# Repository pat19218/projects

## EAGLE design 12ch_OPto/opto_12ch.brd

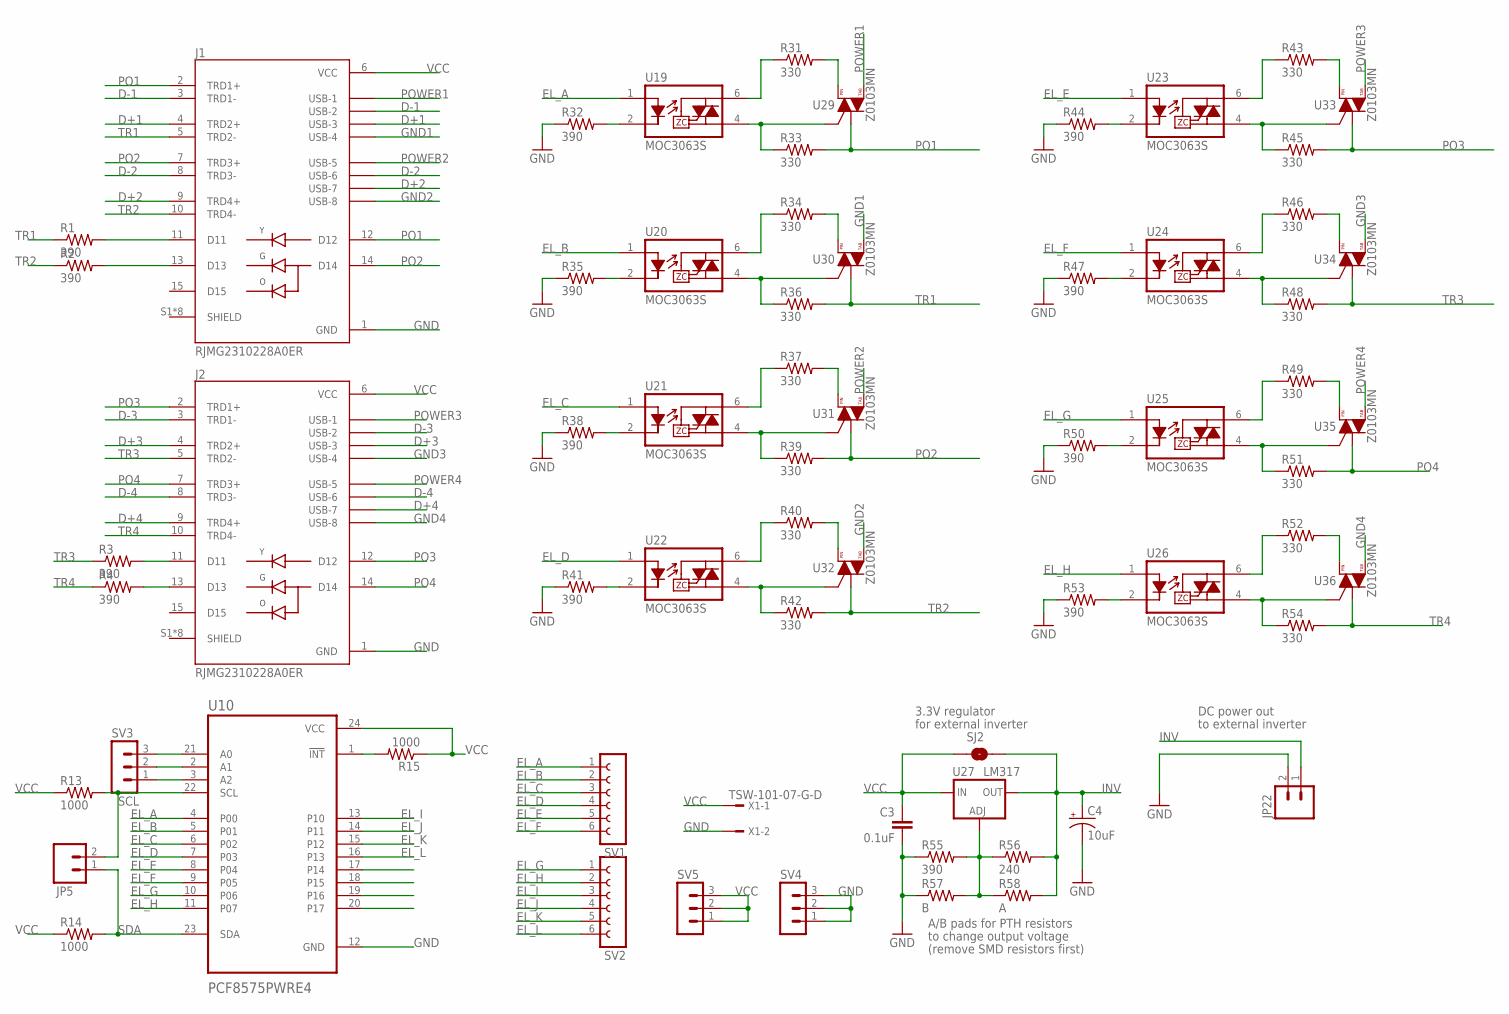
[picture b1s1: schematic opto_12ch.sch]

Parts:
C3: 0.1uF; 0603-CAP
C4: 10uF; EIA3216
J1, J2: RJMG2310228A0ER; AMPHENOL_RJMG2310228A0ER
JP5, JP22: M02PTH; 1X02
R1, R2, R3, R4, R32, R35, R38, R41, R44, R47, R50, R53, R55: 390; 0603-RES
R13, R14, R15: 1000; 0603-RES
R31, R33, R34, R36, R37, R39, R40, R42, R43, R45, R46, R48, R49, R51, R52, R54: 330; 0603-RES
R56: 240; 0603-RES
R57: B; AXIAL-0.4
R58: A; AXIAL-0.4
SJ2: SOLDERJUMPERNO; SJ_2S-NO
SV1, SV2: FE06-1; FE06
SV3, SV4, SV5: MA03-1
U10: PCF8575PWRE4; SOP65P640X120-24N
U19, U20, U21, U22, U23, U24, U25, U26: MOC3063S; DIP8SMD
U27: LM317; V-REG_DPACK
U29, U30, U31, U32, U33, U34, U35, U36: Z0103MN; SOT223
X1: TSW-101-07-G-D; TSW-101-XX-G-D

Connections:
D+1: J1.4 (TRD2+), J1.U13 (USB-3)
D+2: J1.9 (TRD4+), J1.U23 (USB-7)
D+3: J2.4 (TRD2+), J2.U13 (USB-3)
D+4: J2.9 (TRD4+), J2.U23 (USB-7)
D-1: J1.3 (TRD1-), J1.U12 (USB-2)
D-2: J1.8 (TRD3-), J1.U22 (USB-6)
D-3: J2.3 (TRD1-), J2.U12 (USB-2)
D-4: J2.8 (TRD3-), J2.U22 (USB-6)
EL_A: SV1.1, U10.4 (P00), U19.1 (A)
EL_B: SV1.2, U10.5 (P01), U20.1 (A)
EL_C: SV1.3, U10.6 (P02), U21.1 (A)
EL_D: SV1.4, U10.7 (P03), U22.1 (A)
EL_E: SV1.5, U10.8 (P04), U23.1 (A)
EL_F: SV1.6, U10.9 (P05), U24.1 (A)
EL_G: SV2.1, U10.10 (P06), U25.1 (A)
EL_H: SV2.2, U10.11 (P07), U26.1 (A)
EL_I: SV2.3, U10.13 (P10)
EL_J: SV2.4, U10.14 (P11)
EL_K: SV2.5, U10.15 (P12)
EL_L: SV2.6, U10.16 (P13)
GND: C3.2, C4.C (-), J1.1 (GND), J2.1 (GND), JP22.2, R32.1, R35.1, R38.1, R41.1, R44.1, R47.1, R50.1, R53.1, R55.1, R57.P$1 (1), SV4.1, SV4.2, SV4.3, U10.12 (GND), X1.2
GND1: J1.U14 (USB-4), U30.4 (T2)
GND2: J1.U24 (USB-8), U32.4 (T2)
GND3: J2.U14 (USB-4), U34.4 (T2)
GND4: J2.U24 (USB-8), U36.4 (T2)
INV: C4.A (+), JP22.1, R56.2, R58.P$2 (2), SJ2.2, U27.4 (OUT)
unnamed: J2.11 (D11), R3.2
unnamed: J2.13 (D13), R4.2
unnamed: SV3.3, U10.21 (A0)
unnamed: SV3.2, U10.2 (A1)
unnamed: SV3.1, U10.3 (A2)
unnamed: R15.2, U10.1 (!INT)
unnamed: J1.11 (D11), R1.2
unnamed: J1.13 (D13), R2.2
unnamed: R33.1, U19.4 (T2), U29.3 (G)
unnamed: R32.2, U19.2 (K)
unnamed: R31.1, U19.6 (T1)
unnamed: R36.1, U20.4 (T2), U30.3 (G)
unnamed: R35.2, U20.2 (K)
unnamed: R34.1, U20.6 (T1)
unnamed: R39.1, U21.4 (T2), U31.3 (G)
unnamed: R38.2, U21.2 (K)
unnamed: R37.1, U21.6 (T1)
unnamed: R42.1, U22.4 (T2), U32.3 (G)
unnamed: R41.2, U22.2 (K)
unnamed: R40.1, U22.6 (T1)
unnamed: R45.1, U23.4 (T2), U33.3 (G)
unnamed: R44.2, U23.2 (K)
unnamed: R43.1, U23.6 (T1)
unnamed: R48.1, U24.4 (T2), U34.3 (G)
unnamed: R47.2, U24.2 (K)
unnamed: R46.1, U24.6 (T1)
unnamed: R51.1, U25.4 (T2), U35.3 (G)
unnamed: R50.2, U25.2 (K)
unnamed: R49.1, U25.6 (T1)
unnamed: R54.1, U26.4 (T2), U36.3 (G)
unnamed: R53.2, U26.2 (K)
unnamed: R52.1, U26.6 (T1)
unnamed: R55.2, R56.1, R57.P$2 (2), R58.P$1 (1), U27.1 (ADJ)
unnamed: R31.2, U29.2 (T2)
unnamed: R34.2, U30.2 (T2)
unnamed: R37.2, U31.2 (T2)
unnamed: R40.2, U32.2 (T2)
unnamed: R43.2, U33.2 (T2)
unnamed: R46.2, U34.2 (T2)
unnamed: R49.2, U35.2 (T2)
unnamed: R52.2, U36.2 (T2)
PO1: J1.2 (TRD1+), J1.12 (D12), R33.2, U29.1 (T1)
PO2: J1.7 (TRD3+), J1.14 (D14), R39.2, U31.1 (T1)
PO3: J2.2 (TRD1+), J2.12 (D12), R45.2, U33.1 (T1)
PO4: J2.7 (TRD3+), J2.14 (D14), R51.2, U35.1 (T1)
POWER1: J1.U11 (USB-1), U29.4 (T2)
POWER2: J1.U21 (USB-5), U31.4 (T2)
POWER3: J2.U11 (USB-1), U33.4 (T2)
POWER4: J2.U21 (USB-5), U35.4 (T2)
SCL: JP5.2, R13.2, U10.22 (SCL)
SDA: JP5.1, R14.2, U10.23 (SDA)
TR1: J1.5 (TRD2-), R1.1, R36.2, U30.1 (T1)
TR2: J1.10 (TRD4-), R2.1, R42.2, U32.1 (T1)
TR3: J2.5 (TRD2-), R3.1, R48.2, U34.1 (T1)
TR4: J2.10 (TRD4-), R4.1, R54.2, U36.1 (T1)
VCC: C3.1, J1.6 (VCC), J2.6 (VCC), R13.1, R14.1, R15.1, SJ2.1, SV5.1, SV5.2, SV5.3, U10.24 (VCC), U27.3 (IN), X1.1

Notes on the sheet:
DC power out
to external inverter
3.3V regulator
for external inverter
A/B pads for PTH resistors
to change output voltage
(remove SMD resistors first)

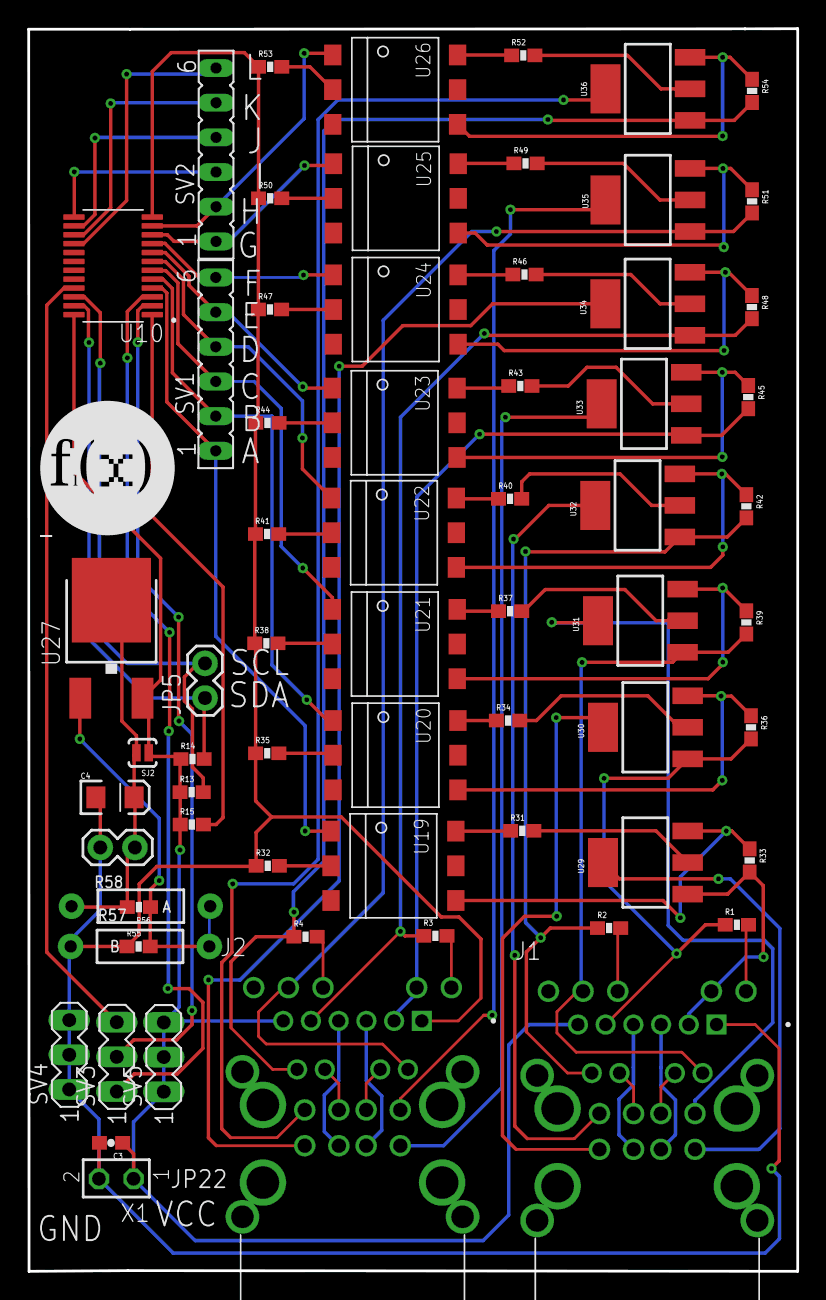
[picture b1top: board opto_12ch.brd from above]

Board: 2 copper layers, 56.3 x 91.0 mm, 66 parts (0 on the bottom side), 82 nets.

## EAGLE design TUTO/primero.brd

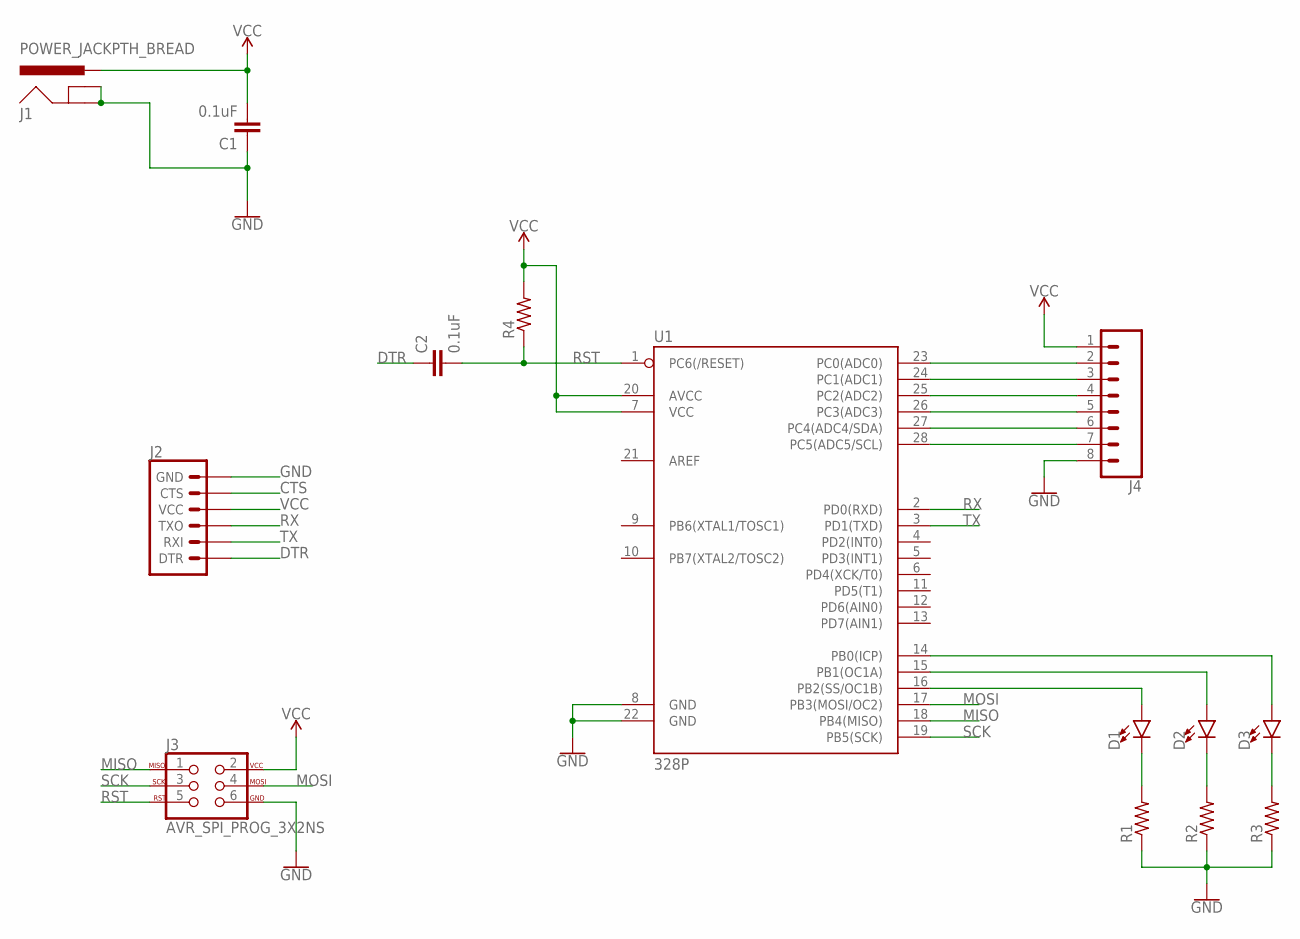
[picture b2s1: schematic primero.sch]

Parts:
C1, C2: 0.1uF; CAP-PTH-SMALL-KIT
D1, D2, D3: LED5MM; LED_5MM
J1: POWER_JACKPTH_BREAD; POWER_JACK_PTH_BREAD
J2: 6_PIN_SERIAL_TARGET; 1X06
J3: AVR_SPI_PROG_3X2NS; 2X3-NS
J4: CONN_08"; 1X08
R1, R2, R3, R4: R-US_0204/5; 0204/5
U1: 328P; DIP28

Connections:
CTS: J2.5 (CTS)
DTR: C2.1, J2.1 (DTR)
GND: C1.1, J1.GND, J1.GNDBREAK, J2.6 (GND), J3.6, J4.8, R1.1, R2.1, R3.1, U1.8 (GND), U1.22 (GND)
MISO: J3.1, U1.18 (PB4(MISO))
MOSI: J3.4, U1.17 (PB3(MOSI/OC2))
unnamed: J4.2, U1.23 (PC0(ADC0))
unnamed: J4.3, U1.24 (PC1(ADC1))
unnamed: J4.4, U1.25 (PC2(ADC2))
unnamed: J4.5, U1.26 (PC3(ADC3))
unnamed: J4.6, U1.27 (PC4(ADC4/SDA))
unnamed: J4.7, U1.28 (PC5(ADC5/SCL))
unnamed: D3.A, U1.14 (PB0(ICP))
unnamed: D3.K (C), R3.2
unnamed: D2.K (C), R2.2
unnamed: D1.K (C), R1.2
unnamed: D2.A, U1.15 (PB1(OC1A))
unnamed: D1.A, U1.16 (PB2(SS/OC1B))
RST: C2.2, J3.5, R4.1, U1.1 (PC6(/RESET))
RX: J2.3 (TXO), U1.2 (PD0(RXD))
SCK: J3.3, U1.19 (PB5(SCK))
TX: J2.2 (RXI), U1.3 (PD1(TXD))
VCC: C1.2, J1.PWR, J2.4 (VCC), J3.2, J4.1, R4.2, U1.7 (VCC), U1.20 (AVCC)

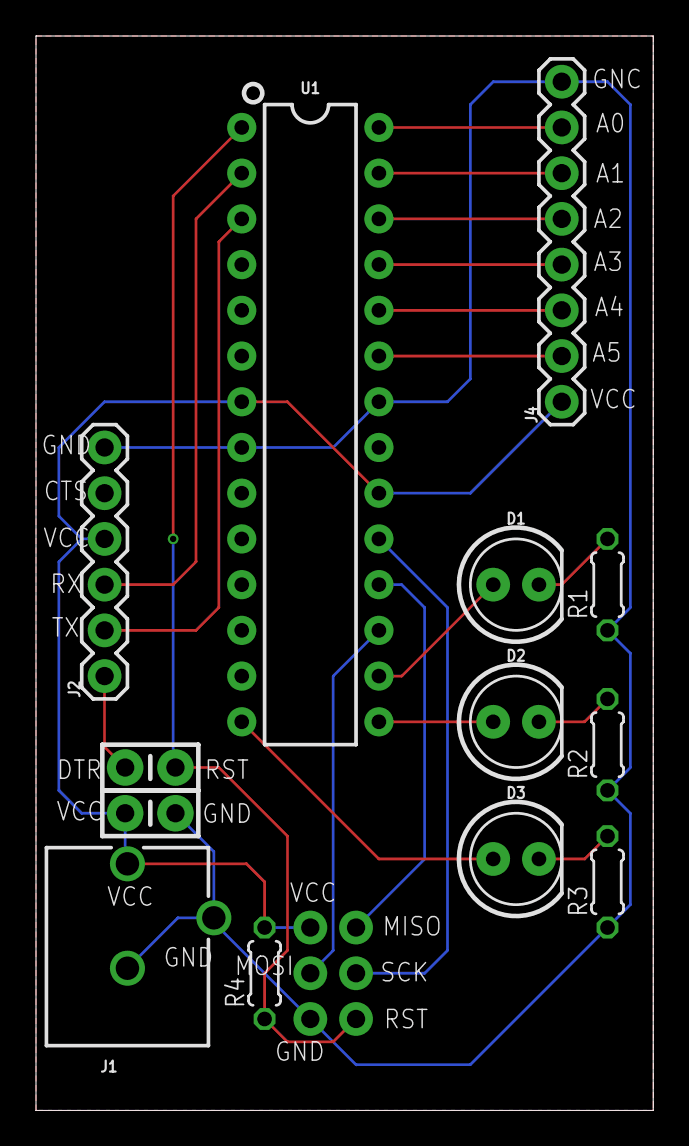
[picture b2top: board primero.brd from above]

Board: 2 copper layers, 34.3 x 59.7 mm, 14 parts (1 on the bottom side), 21 nets.

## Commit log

2022-10-28 optimiz
    Se redujo lo mayor posible las dimensiones de la placa
2022-10-28 Libs
2022-10-29 last edits

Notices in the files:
parts and their libraries:
SparkFun-Capacitors: Licensing: Creative Commons ShareAlike 4.0 International - https://creativecommons.org/licenses/by-sa/4.0
